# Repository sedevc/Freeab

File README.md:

Freeab
======

Control unit for automatic wood chip burner

####Dependency

python-sqlite3, python-colorama, python-dev

####Schematic

####IO-mindmap

####Flowchart

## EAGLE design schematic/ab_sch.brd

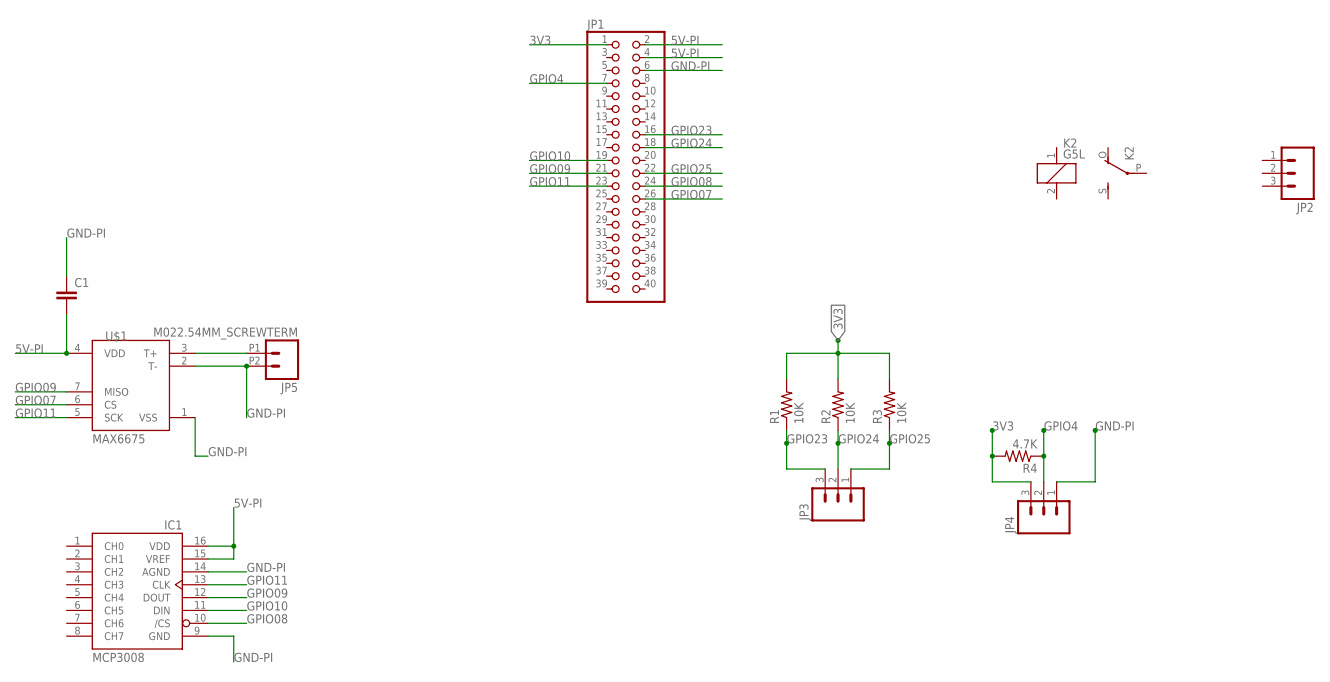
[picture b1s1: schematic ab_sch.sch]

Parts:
C1: CAPKIT; CAP-PTH-SMALL-KIT
IC1: MCP3008; DIL16
JP1: PINHD-2X20; 2X20
JP2, JP3, JP4: M03SCREW; SCREWTERMINAL-3.5MM-3
JP5: M022.54MM_SCREWTERM; 1X02_2.54_SCREWTERM
K2: G5L; G5LE
R1, R2, R3: 10K; 0207/10
R4: 4.7K; 0207/10
U$1: MAX6675; SO08-MAX6675

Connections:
3V3: JP1.1 (3V3), JP4.3, R1.2, R2.2, R3.2, R4.2
5V-PI: C1.2, IC1.15 (VREF), IC1.16 (VDD), JP1.2, JP1.4, U$1.4 (VDD)
GND-PI: C1.1, IC1.9 (GND), IC1.14 (AGND), JP1.6, JP4.1, JP5.P2 (2), U$1.1 (VSS), U$1.2 (T-)
GPIO4: JP1.7, JP4.2, R4.1
GPIO07: JP1.26, U$1.6 (CS)
GPIO08: IC1.10 (/CS), JP1.24
GPIO09: IC1.12 (DOUT), JP1.21, U$1.7 (MISO)
GPIO10: IC1.11 (DIN), JP1.19
GPIO11: IC1.13 (CLK), JP1.23, U$1.5 (SCK)
GPIO23: JP1.16, JP3.3, R1.1
GPIO24: JP1.18, JP3.2, R2.1
GPIO25: JP1.22, JP3.1, R3.1
unnamed: JP5.P1 (1), U$1.3 (T+)

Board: 2 copper layers, 13 parts (0 on the bottom side), 13 nets, no tracks yet.

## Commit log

2014-09-06 Freeab
    Control unit for automatic woodchip boiler
2014-09-06 IO
    I/O list as mind map
2014-09-06 Flowchart
    upload flowchart
2014-09-06 sourcecode
2014-09-06 Deleted pyc files
2014-09-06 Schematic
    Eagle files
2014-09-06 pic
    upload pictures
2014-09-06 Update flowschart
    w/ max-seq, idle-seq.
2014-09-06 flowchart png
2014-09-06 update w/ info
2014-09-08 Video on first run.

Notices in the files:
parts and their libraries:
SparkFun-Connectors: Licensing: Creative Commons ShareAlike 4.0 International - https://creativecommons.org/licenses/by-sa/4.0
